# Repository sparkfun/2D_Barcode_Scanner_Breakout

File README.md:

2D Barcode Scanner Breakout
========================================

[*2D Barcode Scanner Breakout (BOB-18088)*](https://www.sparkfun.com/products/18088)

The DYScan DE2120 is one of the coolest little barcode scanners we've ever seen. This tiny "scan engine" will read 20 different barcode symbologies — both 1D and 2D! This is achieved by using a camera coupled with on-board image processing to identify and decode everything from UPC codes to QR codes. The module also features two LEDs: one for illumination and one to project the red line that you're used to seeing from laser-based scanners. 

This breakout board makes it easy to explore all of the capabilities of the DE2120 without dealing with finicky flat flex cables. The scanner's USB interface is exposed via the on-board USB-C connector. A buzzer and status LED are connected to the module through appropriate drive circuits and a pushbutton tactile switch is provided on the "trigger" pin. When you're ready to incorporate the module into your embedded project, you can leverage the 5 pin header for direct access to the TTL serial pins, power pins, and trigger input.

The module can be configured either by using the serial interface or by scanning command barcodes found in the datasheet.

Repository Contents
-------------------
* **/Documentation** - Datasheet & Settings Manual
* **/Hardware** - Eagle design files (.brd, .sch)

Documentation
--------------
* [SparkFun DE2120 Arduino Library](https://github.com/sparkfun/SparkFun_DE2120_Arduino_Library)
* [SparkFun DE2120 Python Package](https://github.com/sparkfun/DE2120_Py)
* [2D Barcode Scanner Breakout Hookup Guide](https://learn.sparkfun.com/tutorials/2d-barcode-scanner-breakout-hookup-guide)

Product Versions

* [BOB-18088](https://www.sparkfun.com/products/18088)
* [SPX-16441](https://www.sparkfun.com/products/16441)
* [SPX-16410](https://www.sparkfun.com/products/16410)

License Information
-------------------

This product is _**open source**_! 

Please review the LICENSE.md file for license information. 

If you have any questions or concerns on licensing, please contact technical support on our [SparkFun forums](https://forum.sparkfun.com/viewforum.php?f=152).

Distributed as-is; no warranty is given.

- Your friends at SparkFun.

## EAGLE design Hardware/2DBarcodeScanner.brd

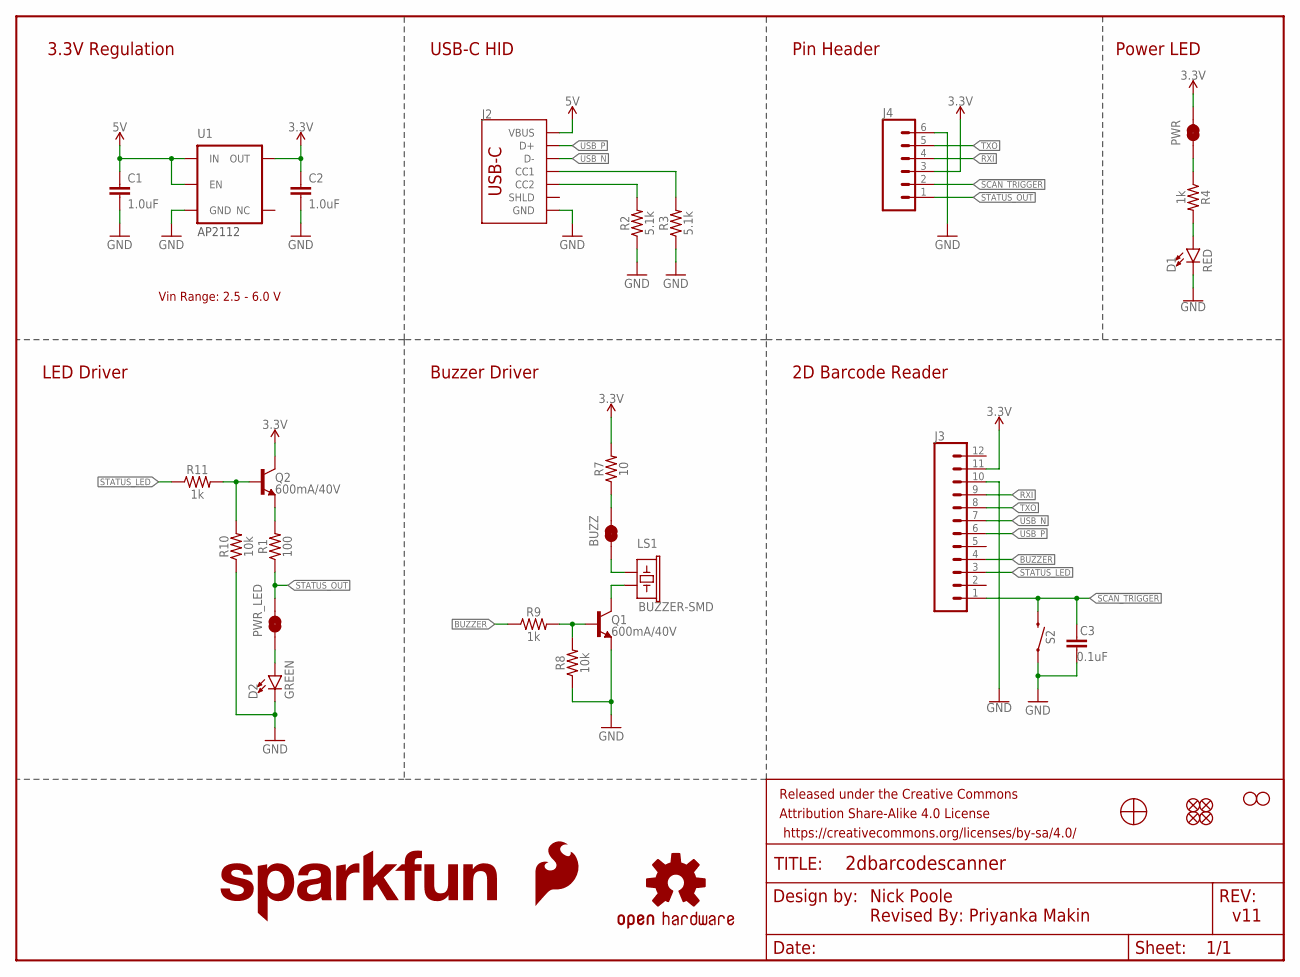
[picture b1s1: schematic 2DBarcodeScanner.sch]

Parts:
BUZZ: JUMPER-SMT_2_NC_TRACE_SILK; SMT-JUMPER_2_NC_TRACE_SILK
C1, C2: 1.0uF; 0603
C3: 0.1uF; 0603
D1: RED; LED-0603
D2: GREEN; LED-0603
FD1, FD2, FD3, FD4: FIDUCIALUFIDUCIAL; FIDUCIAL-MICRO
FRAME1: FRAME-LETTER; CREATIVE_COMMONS
H2, H3: STAND-OFF
J2: USB_C_2-LAYER_PADS; USB-C-16P-2LAYER-PADS
J3: CONN_12FPC_12_0.5MM; FPC_12_0.5MM
J4: CONN_06NO_SILK_FEMALE_PTH; 1X06_NO_SILK
LOGO1: OSHW-LOGOS; OSHW-LOGO-S
LOGO2: SFE_LOGO_FLAME.1_INCH; SFE_LOGO_FLAME_.1
LOGO3: SFE_LOGO_NAME.1_INCH; SFE_LOGO_NAME_.1
LS1: BUZZER-SMD; BUZZER-CCV
PWR: JUMPER-SMT_2_NC_TRACE_SILK; SMT-JUMPER_2_NC_TRACE_SILK
PWR_LED: JUMPER-SMT_2_NC_TRACE_SILK; SMT-JUMPER_2_NC_TRACE_SILK
Q1, Q2: 600mA/40V; SOT23-3
R1: 100; 0603
R2, R3: 5.1k; 0603
R4, R9, R11: 1k; 0603
R7: 10; 0603
R8, R10: 10k; 0603
S2: MOMENTARY-SWITCH-SPST-SMD-5.2MM-TALL; TACTILE_SWITCH_SMD_5.2MM
U1: 3.3V; SOT23-5
U2: BARCODE_SCANNER_MOUNT

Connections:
3.3V: C2.1, J3.11, J4.3, PWR.2, Q2.3 (C), R7.2, U1.5 (OUT)
5V: C1.1, J2.VBUS1 (VBUS), J2.VBUS2 (VBUS), U1.1 (IN), U1.3 (EN)
!SCAN_TRIGGER!: C3.1, J3.1, J4.2, S2.3 (2)
BUZZER: J3.4, R9.1
CC3: J2.A5 (CC1), R3.2
CC4: J2.B5 (CC2), R2.2
GND: C1.2, C2.2, C3.2, D1.C, D2.C, J2.GND, J2.GND2 (GND), J3.10, J4.6, Q1.2 (E), R2.1, R3.1, R8.1, R10.1, S2.1, U1.2 (GND)
unnamed: BUZZ.2, R7.1
unnamed: LS1.- (2), Q1.3 (C)
unnamed: BUZZ.1, LS1.+ (1)
unnamed: Q2.2 (E), R1.2
unnamed: Q1.1 (B), R8.2, R9.2
unnamed: PWR.1, R4.1
unnamed: Q2.1 (B), R10.2, R11.2
unnamed: D2.A, PWR_LED.1
unnamed: D1.A, R4.2
RXI: J3.9, J4.4
STATUS_LED: J3.3, R11.1
STATUS_OUT: J4.1, PWR_LED.2, R1.1
TXO: J3.8, J4.5
USB_N: J2.A7 (D-), J2.B7 (D-), J3.7
USB_P: J2.A6 (D+), J2.B6 (D+), J3.6

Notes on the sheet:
3.3V Regulation
AP2112
Pin Header
2D Barcode Reader
LED Driver
Buzzer Driver
USB-C HID
Power LED
Nick Poole Revised By: Priyanka Makin
v11
Vin Range: 2.5 - 6.0 V

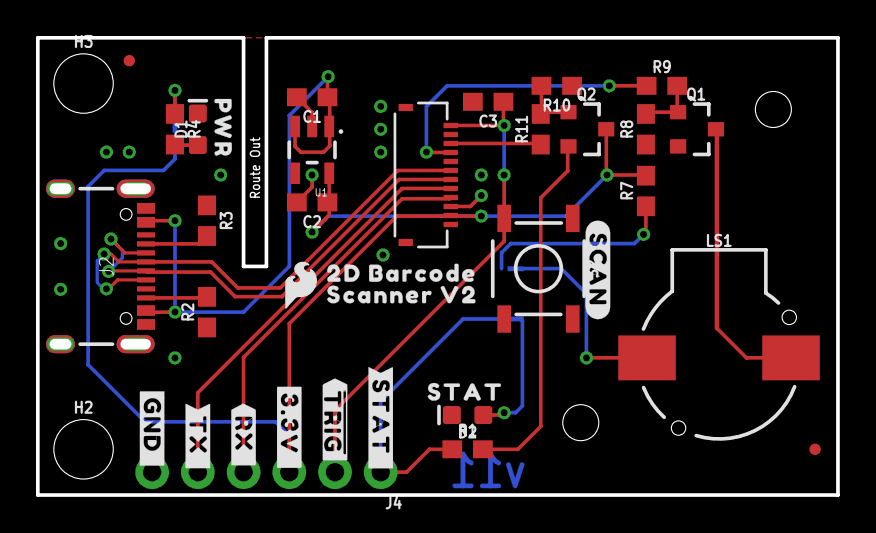
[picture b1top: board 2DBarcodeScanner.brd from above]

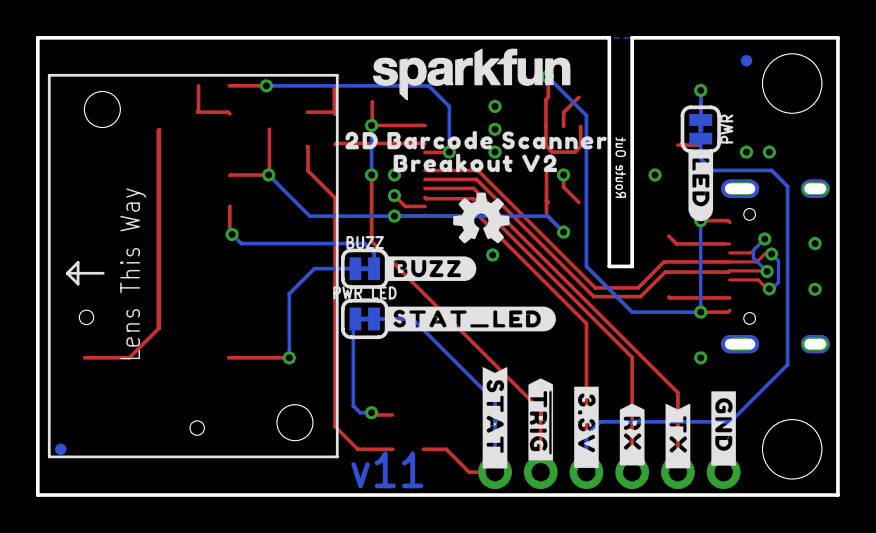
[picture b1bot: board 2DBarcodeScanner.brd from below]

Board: 2 copper layers, 44.1 x 25.0 mm, 58 parts (19 on the bottom side), 22 nets.

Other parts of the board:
U$1, U$7: ##TRIG##0
U$2, U$21: #STAT_#0
U$3: STAT0
U$4: #SCAN#0
U$5: #BUZZ#0
U$6: #STAT_LED#0
U$8: PWR0
U$9: #LED#0
U$10: SCANNER_V20
U$11: BREAKOUT_V20
U$12: 2D_BARCODE_SCANNER0
U$17: 2D_BARCODE0
U$26, U$27: #TX_#0
U$28, U$29: #3#3V_#0
U$30, U$31: #RX_#0
U$32, U$33: #GND_#0

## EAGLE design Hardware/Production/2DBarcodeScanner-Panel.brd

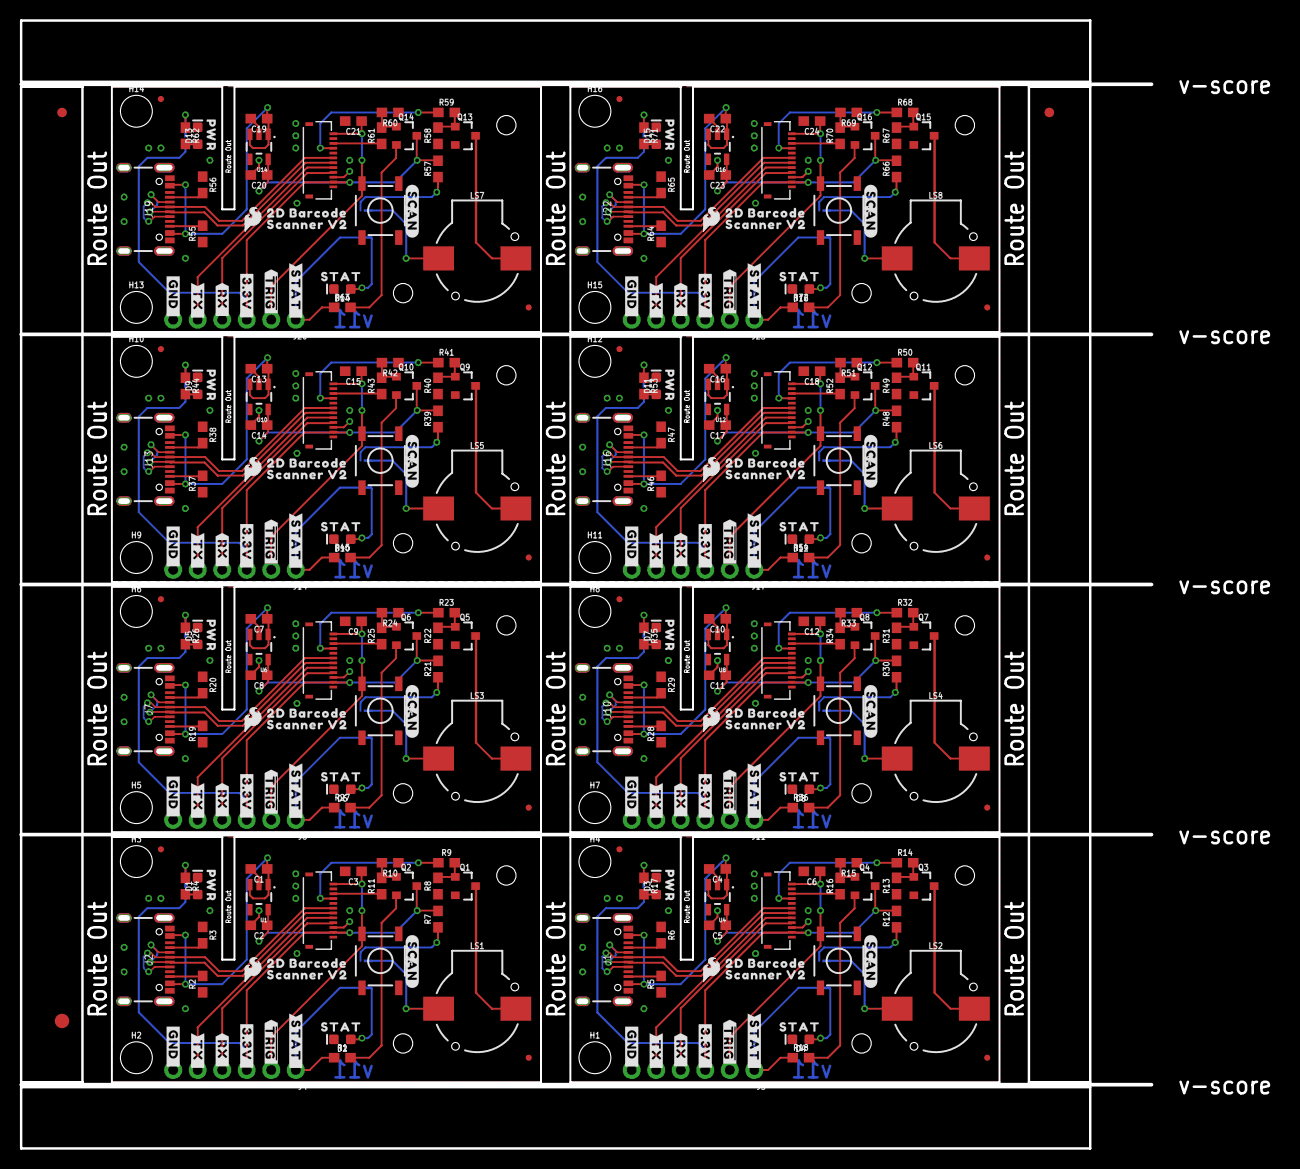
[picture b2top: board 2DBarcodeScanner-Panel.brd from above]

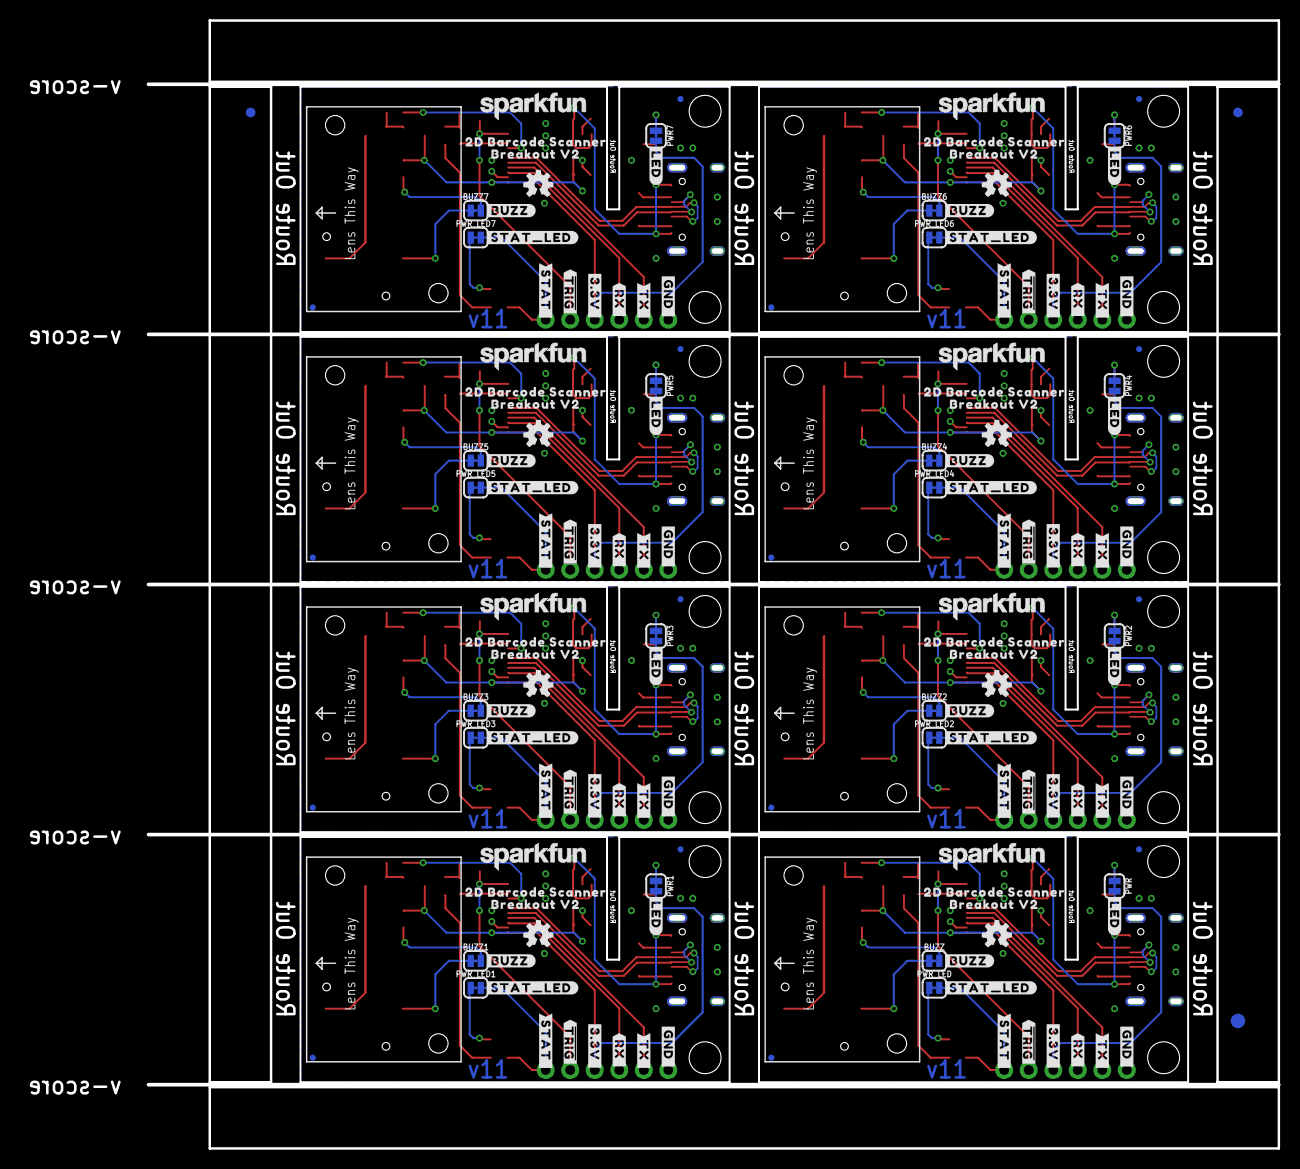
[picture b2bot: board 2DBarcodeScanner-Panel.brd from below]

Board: 2 copper layers, 130.1 x 116.5 mm, 462 parts (155 on the bottom side), 176 nets.

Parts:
BUZZ, BUZZ1, BUZZ2, BUZZ3, BUZZ4, BUZZ5, BUZZ6, BUZZ7: JUMPER-SMT_2_NC_TRACE_SILK; SMT-JUMPER_2_NC_TRACE_SILK
C1, C2, C4, C5, C7, C8, C10, C11, C13, C14, C16, C17, C19, C20, C22, C23: 1.0uF; 0603
C3, C6, C9, C12, C15, C18, C21, C24: 0.1uF; 0603
D1, D3, D5, D7, D9, D11, D13, D15: RED; LED-0603
D2, D4, D6, D8, D10, D12, D14, D16: GREEN; LED-0603
E$1, E$2, E$3, E$4: FIDUCIAL-1X2
E$5, E$6: FIDUCIAL-1.5X3
FD1, FD2, FD3, FD4, FD5, FD6, FD7, FD8, FD9, FD10, FD11, FD12, FD13, FD14, FD15, FD16, FD17, FD18, FD19, FD20, FD21, FD22, FD23, FD24, FD25, FD26, FD27, FD28, FD29, FD30, FD31, FD32: FIDUCIALUFIDUCIAL; FIDUCIAL-MICRO
H1, H2, H3, H4, H5, H6, H7, H8, H9, H10, H11, H12, H13, H14, H15, H16: STAND-OFF
J1, J2, J7, J10, J13, J16, J19, J22: USB-C-16P-2LAYER-PADS
J3, J6, J9, J12, J15, J18, J21, J24: FPC_12_0.5MM
J4, J5, J8, J11, J14, J17, J20, J23: 1X06_NO_SILK
LOGO1, LOGO4, LOGO7, LOGO10, LOGO13, LOGO16, LOGO19, LOGO22: OSHW-LOGOS; OSHW-LOGO-S
LOGO2, LOGO5, LOGO8, LOGO11, LOGO14, LOGO17, LOGO20, LOGO23: SFE_LOGO_FLAME.1_INCH; SFE_LOGO_FLAME_.1
LOGO3, LOGO6, LOGO9, LOGO12, LOGO15, LOGO18, LOGO21, LOGO24: SFE_LOGO_NAME.1_INCH; SFE_LOGO_NAME_.1
LS1, LS2, LS3, LS4, LS5, LS6, LS7, LS8: BUZZER-SMD; BUZZER-CCV
PWR, PWR1, PWR2, PWR3, PWR4, PWR5, PWR6, PWR7: JUMPER-SMT_2_NC_TRACE_SILK; SMT-JUMPER_2_NC_TRACE_SILK
PWR_LED, PWR_LED1, PWR_LED2, PWR_LED3, PWR_LED4, PWR_LED5, PWR_LED6, PWR_LED7: JUMPER-SMT_2_NC_TRACE_SILK; SMT-JUMPER_2_NC_TRACE_SILK
Q1, Q2, Q3, Q4, Q5, Q6, Q7, Q8, Q9, Q10, Q11, Q12, Q13, Q14, Q15, Q16: 600mA/40V; SOT23-3
R1, R18, R27, R36, R45, R54, R63, R72: 100; 0603
R2, R3, R5, R6, R19, R20, R28, R29, R37, R38, R46, R47, R55, R56, R64, R65: 5.1k; 0603
R4, R9, R11, R14, R16, R17, R23, R25, R26, R32, R34, R35, R41, R43, R44, R50, R52, R53, R59, R61, R62, R68, R70, R71: 1k; 0603
R7, R12, R21, R30, R39, R48, R57, R66: 10; 0603
R8, R10, R13, R15, R22, R24, R31, R33, R40, R42, R49, R51, R58, R60, R67, R69: 10k; 0603
S1, S2, S3, S4, S5, S6, S7, S8: MOMENTARY-SWITCH-SPST-SMD-5.2MM-TALL; TACTILE_SWITCH_SMD_5.2MM
U1, U4, U6, U8, U10, U12, U14, U16: 3.3V; SOT23-5
U2, U3, U5, U7, U9, U11, U13, U15: BARCODE_SCANNER_MOUNT
U$1, U$7, U$40, U$41, U$62, U$63, U$84, U$85, U$106, U$107, U$128, U$129, U$150, U$151, U$172, U$173: ##TRIG##0
U$2, U$13, U$16, U$21, U$45, U$48, U$67, U$70, U$89, U$92, U$111, U$114, U$133, U$136, U$155, U$158: #STAT_#0
U$3, U$14, U$46, U$68, U$90, U$112, U$134, U$156: STAT0
U$4, U$35, U$57, U$79, U$101, U$123, U$145, U$167: #SCAN#0
U$5, U$36, U$58, U$80, U$102, U$124, U$146, U$168: #BUZZ#0
U$6, U$39, U$61, U$83, U$105, U$127, U$149, U$171: #STAT_LED#0
U$8, U$37, U$59, U$81, U$103, U$125, U$147, U$169: PWR0
U$9, U$38, U$60, U$82, U$104, U$126, U$148, U$170: #LED#0
U$10, U$42, U$64, U$86, U$108, U$130, U$152, U$174: SCANNER_V20
U$11, U$43, U$65, U$87, U$109, U$131, U$153, U$175: BREAKOUT_V20
U$12, U$44, U$66, U$88, U$110, U$132, U$154, U$176: 2D_BARCODE_SCANNER0
U$15, U$17, U$47, U$69, U$91, U$113, U$135, U$157: 2D_BARCODE0
U$18, U$19, U$28, U$29, U$49, U$50, U$71, U$72, U$93, U$94, U$115, U$116, U$137, U$138, U$159, U$160: #3#3V_#0
U$20, U$22, U$26, U$27, U$51, U$52, U$73, U$74, U$95, U$96, U$117, U$118, U$139, U$140, U$161, U$162: #TX_#0
U$23, U$24, U$30, U$31, U$53, U$54, U$75, U$76, U$97, U$98, U$119, U$120, U$141, U$142, U$163, U$164: #RX_#0
U$25, U$32, U$33, U$34, U$55, U$56, U$77, U$78, U$99, U$100, U$121, U$122, U$143, U$144, U$165, U$166: #GND_#0

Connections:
3.3V: C2.1, J3.11, J4.3, PWR.2, Q2.3, R7.2, U1.5
3.3V1: C5.1, J5.3, J6.11, PWR1.2, Q4.3, R12.2, U4.5
3.3V2: C8.1, J8.3, J9.11, PWR2.2, Q6.3, R21.2, U6.5
3.3V3: C11.1, J11.3, J12.11, PWR3.2, Q8.3, R30.2, U8.5
3.3V4: C14.1, J14.3, J15.11, PWR4.2, Q10.3, R39.2, U10.5
3.3V5: C17.1, J17.3, J18.11, PWR5.2, Q12.3, R48.2, U12.5
3.3V6: C20.1, J20.3, J21.11, PWR6.2, Q14.3, R57.2, U14.5
3.3V7: C23.1, J23.3, J24.11, PWR7.2, Q16.3, R66.2, U16.5
5V: C1.1, J2.VBUS1, J2.VBUS2, U1.1, U1.3
5V1: C4.1, J1.VBUS1, J1.VBUS2, U4.1, U4.3
5V2: C7.1, J7.VBUS1, J7.VBUS2, U6.1, U6.3
5V3: C10.1, J10.VBUS1, J10.VBUS2, U8.1, U8.3
5V4: C13.1, J13.VBUS1, J13.VBUS2, U10.1, U10.3
5V5: C16.1, J16.VBUS1, J16.VBUS2, U12.1, U12.3
5V6: C19.1, J19.VBUS1, J19.VBUS2, U14.1, U14.3
5V7: C22.1, J22.VBUS1, J22.VBUS2, U16.1, U16.3
!SCAN_TRIGGER!: C3.1, J3.1, J4.2, S2.3
!SCAN_TRIGGER!1: C6.1, J5.2, J6.1, S1.3
!SCAN_TRIGGER!2: C9.1, J8.2, J9.1, S3.3
!SCAN_TRIGGER!3: C12.1, J11.2, J12.1, S4.3
!SCAN_TRIGGER!4: C15.1, J14.2, J15.1, S5.3
!SCAN_TRIGGER!5: C18.1, J17.2, J18.1, S6.3
!SCAN_TRIGGER!6: C21.1, J20.2, J21.1, S7.3
!SCAN_TRIGGER!7: C24.1, J23.2, J24.1, S8.3
BUZZER: J3.4, R9.1
BUZZER1: J6.4, R14.1
BUZZER2: J9.4, R23.1
BUZZER3: J12.4, R32.1
BUZZER4: J15.4, R41.1
BUZZER5: J18.4, R50.1
BUZZER6: J21.4, R59.1
BUZZER7: J24.4, R68.1
CC1: J1.A5, R6.2
CC2: J1.B5, R5.2
CC3: J2.A5, R3.2
CC4: J2.B5, R2.2
CC5: J7.A5, R20.2
CC6: J7.B5, R19.2
CC7: J10.A5, R29.2
CC8: J10.B5, R28.2
CC9: J13.A5, R38.2
CC10: J13.B5, R37.2
CC11: J16.A5, R47.2
CC12: J16.B5, R46.2
CC13: J19.A5, R56.2
CC14: J19.B5, R55.2
CC15: J22.A5, R65.2
CC16: J22.B5, R64.2
GND: C1.2, C2.2, C3.2, D1.C, D2.C, J2.GND, J2.GND2, J3.10, J4.6, Q1.2, R2.1, R3.1, R8.1, R10.1, S2.1, U1.2
GND1: C4.2, C5.2, C6.2, D3.C, D4.C, J1.GND, J1.GND2, J5.6, J6.10, Q3.2, R5.1, R6.1, R13.1, R15.1, S1.1, U4.2
GND2: C7.2, C8.2, C9.2, D5.C, D6.C, J7.GND, J7.GND2, J8.6, J9.10, Q5.2, R19.1, R20.1, R22.1, R24.1, S3.1, U6.2
GND3: C10.2, C11.2, C12.2, D7.C, D8.C, J10.GND, J10.GND2, J11.6, J12.10, Q7.2, R28.1, R29.1, R31.1, R33.1, S4.1, U8.2
GND4: C13.2, C14.2, C15.2, D9.C, D10.C, J13.GND, J13.GND2, J14.6, J15.10, Q9.2, R37.1, R38.1, R40.1, R42.1, S5.1, U10.2
GND5: C16.2, C17.2, C18.2, D11.C, D12.C, J16.GND, J16.GND2, J17.6, J18.10, Q11.2, R46.1, R47.1, R49.1, R51.1, S6.1, U12.2
GND6: C19.2, C20.2, C21.2, D13.C, D14.C, J19.GND, J19.GND2, J20.6, J21.10, Q13.2, R55.1, R56.1, R58.1, R60.1, S7.1, U14.2
GND7: C22.2, C23.2, C24.2, D15.C, D16.C, J22.GND, J22.GND2, J23.6, J24.10, Q15.2, R64.1, R65.1, R67.1, R69.1, S8.1, U16.2
unnamed: BUZZ.2, R7.1
unnamed: LS1.-, Q1.3
unnamed: BUZZ.1, LS1.+
unnamed: Q2.2, R1.2
unnamed: Q1.1, R8.2, R9.2
unnamed: PWR.1, R4.1
unnamed: Q2.1, R10.2, R11.2
unnamed: D2.A, PWR_LED.1
unnamed: D1.A, R4.2
unnamed: LS2.-, Q3.3
unnamed: Q3.1, R13.2, R14.2
unnamed: Q4.2, R18.2
unnamed: Q4.1, R15.2, R16.2
unnamed: D4.A, PWR_LED1.1
unnamed: BUZZ1.2, R12.1
unnamed: BUZZ1.1, LS2.+
unnamed: PWR1.1, R17.1
unnamed: D3.A, R17.2
unnamed: LS3.-, Q5.3
unnamed: Q5.1, R22.2, R23.2
unnamed: Q6.2, R27.2
unnamed: Q6.1, R24.2, R25.2
unnamed: D6.A, PWR_LED2.1
unnamed: BUZZ2.2, R21.1
unnamed: BUZZ2.1, LS3.+
unnamed: PWR2.1, R26.1
unnamed: D5.A, R26.2
unnamed: LS4.-, Q7.3
unnamed: Q7.1, R31.2, R32.2
unnamed: Q8.2, R36.2
unnamed: Q8.1, R33.2, R34.2
unnamed: D8.A, PWR_LED3.1
unnamed: BUZZ3.2, R30.1
unnamed: BUZZ3.1, LS4.+
unnamed: PWR3.1, R35.1
unnamed: D7.A, R35.2
unnamed: LS5.-, Q9.3
unnamed: Q9.1, R40.2, R41.2
unnamed: Q10.2, R45.2
unnamed: Q10.1, R42.2, R43.2
unnamed: D10.A, PWR_LED4.1
unnamed: BUZZ4.2, R39.1
unnamed: BUZZ4.1, LS5.+
unnamed: PWR4.1, R44.1
unnamed: D9.A, R44.2
unnamed: LS6.-, Q11.3
unnamed: Q11.1, R49.2, R50.2
unnamed: Q12.2, R54.2
unnamed: Q12.1, R51.2, R52.2
unnamed: D12.A, PWR_LED5.1
unnamed: BUZZ5.2, R48.1
unnamed: BUZZ5.1, LS6.+
unnamed: PWR5.1, R53.1
unnamed: D11.A, R53.2
unnamed: LS7.-, Q13.3
unnamed: Q13.1, R58.2, R59.2
unnamed: Q14.2, R63.2
unnamed: Q14.1, R60.2, R61.2
unnamed: D14.A, PWR_LED6.1
unnamed: BUZZ6.2, R57.1
unnamed: BUZZ6.1, LS7.+
unnamed: PWR6.1, R62.1
unnamed: D13.A, R62.2
unnamed: LS8.-, Q15.3
unnamed: Q15.1, R67.2, R68.2
unnamed: Q16.2, R72.2
unnamed: Q16.1, R69.2, R70.2
unnamed: D16.A, PWR_LED7.1
unnamed: BUZZ7.2, R66.1
unnamed: BUZZ7.1, LS8.+
unnamed: PWR7.1, R71.1
unnamed: D15.A, R71.2
RXI: J3.9, J4.4
RXI1: J5.4, J6.9
RXI2: J8.4, J9.9
RXI3: J11.4, J12.9
RXI4: J14.4, J15.9
RXI5: J17.4, J18.9
RXI6: J20.4, J21.9
RXI7: J23.4, J24.9
STATUS_LED: J3.3, R11.1
STATUS_LED1: J6.3, R16.1
STATUS_LED2: J9.3, R25.1
STATUS_LED3: J12.3, R34.1
STATUS_LED4: J15.3, R43.1
STATUS_LED5: J18.3, R52.1
STATUS_LED6: J21.3, R61.1
STATUS_LED7: J24.3, R70.1
STATUS_OUT: J4.1, PWR_LED.2, R1.1
STATUS_OUT1: J5.1, PWR_LED1.2, R18.1
STATUS_OUT2: J8.1, PWR_LED2.2, R27.1
STATUS_OUT3: J11.1, PWR_LED3.2, R36.1
STATUS_OUT4: J14.1, PWR_LED4.2, R45.1
STATUS_OUT5: J17.1, PWR_LED5.2, R54.1
STATUS_OUT6: J20.1, PWR_LED6.2, R63.1
STATUS_OUT7: J23.1, PWR_LED7.2, R72.1
TXO: J3.8, J4.5
TXO1: J5.5, J6.8
TXO2: J8.5, J9.8
TXO3: J11.5, J12.8
TXO4: J14.5, J15.8
TXO5: J17.5, J18.8
TXO6: J20.5, J21.8
TXO7: J23.5, J24.8
USB_N: J2.A7, J2.B7, J3.7
USB_N1: J1.A7, J1.B7, J6.7
USB_N2: J7.A7, J7.B7, J9.7
USB_N3: J10.A7, J10.B7, J12.7
USB_N4: J13.A7, J13.B7, J15.7
USB_N5: J16.A7, J16.B7, J18.7
USB_N6: J19.A7, J19.B7, J21.7
USB_N7: J22.A7, J22.B7, J24.7
USB_P: J2.A6, J2.B6, J3.6
USB_P1: J1.A6, J1.B6, J6.6
USB_P2: J7.A6, J7.B6, J9.6
USB_P3: J10.A6, J10.B6, J12.6
USB_P4: J13.A6, J13.B6, J15.6
USB_P5: J16.A6, J16.B6, J18.6
USB_P6: J19.A6, J19.B6, J21.6
USB_P7: J22.A6, J22.B6, J24.6

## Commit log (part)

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2021-03-19 Add datasheets to documentation folder
2021-03-30 Update SPX design for reds
    Changes made:
    Switched out 12-pin ribbon cable connector for the one used on the RTK
    Added jumper on the buzzer
    Added power LED
    Updated names/version numbers
    Added fiducials
2021-03-30 Update silkscreen
2021-03-30 Silkscreen
2021-03-30 Ran schematic/board checklists
2021-03-30 Change out green stat LED for yellow
    Pull-up resistor 470 --> 1k ohm
2021-03-30 Switch yellow stat LED out for blue
2021-04-01 Design Review Changes
    Update schematic frame
    Dimension width 0.008
    Increased width of GND polygon
    Moved v10 label on bottom
    Moved bottom jumpers in-line
    Added measures
2021-04-02 QC Double Check Changes
2021-04-02 Panelize and generate gerbers
2021-04-02 Make zip folder of eagle files
2021-04-30 Flip TX and RX pins
2021-04-30 Update version number and re-panelize v11
2021-04-30 Update panel name and create zip folder of eagle files
2021-05-21 Switch status LED from blue to green and change pull-up to 100 ohms
2021-05-21 Re-panelize for BOM change
2021-05-26 Update README
    Updating README.md file for product release.
2026-02-10 Update silk for V2 board
2026-02-24 misc update
2026-02-24 Add new production files with silk change
2026-02-26 Add gerbers for new scanner

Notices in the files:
parts and their libraries:
SparkFun-Capacitors: Licensing: Creative Commons ShareAlike 4.0 International - https://creativecommons.org/licenses/by-sa/4.0
SparkFun-Aesthetics: Released under the Creative Commons Attribution Share-Alike 4.0 License
SparkFun-Aesthetics: https://creativecommons.org/licenses/by-sa/4.0
